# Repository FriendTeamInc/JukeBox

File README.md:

<p align="center">An affordable, adorable, powerful hotkey device to run macros, play funny sounds, managing your audio settings, change paint brush settings, configure items in OBS, and so much more!</p>

# Disclaimer
While this project is public, it is not ready for any sort of prime time. Any releases prior to 1.0 are considered beta.

## Docs
TODO

## Desktop Software
Made with Rust and egui for Windows and Linux, curates the user experience with the JukeBox.

### Building
It's as simple as running `cargo build --release`.

### Discord support
Discord, currently, will not provide support to new projects using their RPC protocol. Because of this, JukeBox Desktop will not support Discord out of the box, despite having functionality for it built in. To use the Discord functionality in JukeBox Desktop, you must do the following:
1. Go to https://discord.com/developers/applications/ and log in with your account.
2. Create a new application and name it JukeBoxDesktop.
3. Go to the OAuth2 settings tab.
4. Copy the client ID and client secret down to a safe location.
5. Set the redirect to `https://localhost:61961`. Save your changes.
6. Go to the App Testers settings tab.
7. Add your Discord account as a tester. An email will be sent to your account email, go to your inbox and accept the invite.
8. Build with the following command: `DISCORD_CLIENT_ID="<PUT_CLIENT_ID_HERE>" DISCORD_CLIENT_SECRET="<PUT_CLIENT_SECRET_HERE>" cargo run --features "discord" --release`.

## Device Firmware
TODO

### Building
1. (Linux only) Add yourself to the dialout group with the following: `sudo usermod -a -G dialout $USER`. Install the [RPi Pico udev rules](https://github.com/raspberrypi/picotool/blob/master/udev/99-picotool.rules). Add the following rules:
```
SUBSYSTEM=="usb", \
    ATTRS{idVendor}=="2e8a", \
    ATTRS{idProduct}=="000c", \
    TAG+="uaccess" \
    MODE="660", \  
    GROUP="plugdev"
```

2. Install the appropriate target toolchain: `rustup target add thumbv6m-none-eabi`.
3. Install [cmake](https://cmake.org/download/) for tool compilation.
4. (Linux only) Install libudev-dev: `sudo apt install libudev-dev`.
5. Install tools: `cargo install flip-link`.
5. Install tools: `cargo install --locked probe-rs-tools`. This is for installing firmware over Pico probe.
6. Run `cargo run -F "keypad"` to install the keypad firmware to the connected device. You can use pedalpad or knobpad too.

## Case
Made with OpenSCAD 2025.03.31 (development snapshot), protects everything inside the JukeBox. You can get the printable STLs with the `build.sh` script.

## PCB
Made with KiCad 10, the external brains of the JukeBox.

Footprints and models:
- [Cherry/Kailh Switch footprint based on this.](https://github.com/luke-schutt/Pi5Keyboard/blob/main/Pi5-pcb/Pi5Footprints.pretty/Low%20Profile%20GC%20plus%20MX.kicad_mod)

Estimated power usage is 5 volts at 0.1 amps, or 0.5 watts.

### Bill of Materials
| Ref            | Part No.               | Qty | Value | DNP |
|----------------|------------------------|-----|-------|-----|
| R1, R5, R14    | RMCF0402FT1K00         | 3   | 1k    |     |
| R3, R4         | RMCF0402FT27R0         | 2   | 27    |     |
| R6, R7         | RMCF0402FT5K11         | 2   | 5.11k |     |
| R8-11          | RMCF0402FT10K0         | 4   | 10k   |     |
| R12            | RMCF0402FT10K0         | 1   | 10k   |     |
| R13            | RMCF0402FT10R0         | 1   | 10    |     |
| R15            | RMCF0402FT33R0         | 1   | 33    |     |
| C1, C2         | GRM21BR61C106KE15K     | 2   | 10u   |     |
| C3, C4         | GCM1555C1H150JA16D     | 2   | 15p   |     |
| C5, C9, C11-18 | GRM155R71E104KE14J     | 10  | 100n  |     |
| C6-8, C10      | GRM155R60J475ME47D     | 4   | 4.7u  |     |
| L1             | AOTA-B201610S3R3-101-T | 1   | 3.3u  |     |
| D1-12          | 1N4148W-SOD-123        | 12  |       |     |
| D13-24         | WS2812B-2020           | 12  |       |     |
| D25            | 150080GS75000          | 1   |       |     |
| J1             | USB4105-GF-A           | 1   |       |     |
| Q1             | S8050-SOT-23           | 1   |       |     |
| SW1-12         | Keyboard Key Switch    | 12  |       |  X  |
| SW13           | PTS636SKG25SMTR LFS    | 1   |       |     |
| U1             | AZ1117IH-3.3TRG1       | 1   |       |     |
| U2             | W25Q32JVSSIQ           | 1   |       |     |
| U3             | RP2350A                | 1   |       |     |
| U4             | TFTQ-T20ST22ZP01       | 1   |       |  X  |
| U4             | FH34SRJ-22S-0.5SH(50)  | 1   |       |     |
| U5             | CAT24C128WI-GT3        | 1   |       |     |
| Y1             | ABM8-272-T3            | 1   |       |     |

# License
Copyright (c) 2020-2026 Logan "NotQuiteApex" Hickok-Dickson

All programming files, found in [`firmware/`](firmware/), [`software/`](software/), and [`case/`](case/), are licensed under the [MIT license](https://mit-license.org/).

All CAD files, found in [`hardware-pcb/`](hardware-pcb/), unless otherwise provided by an external source such as footprints or 3D models, are licesned under the [CC BY-NC-SA license](https://creativecommons.org/licenses/by-nc-sa/4.0/).

Both licenses can be found with the given links or as files in the root of this repostiory.

If you would like to sell a variation of the board designed by you, reach out and an alternative license can be discussed and granted.

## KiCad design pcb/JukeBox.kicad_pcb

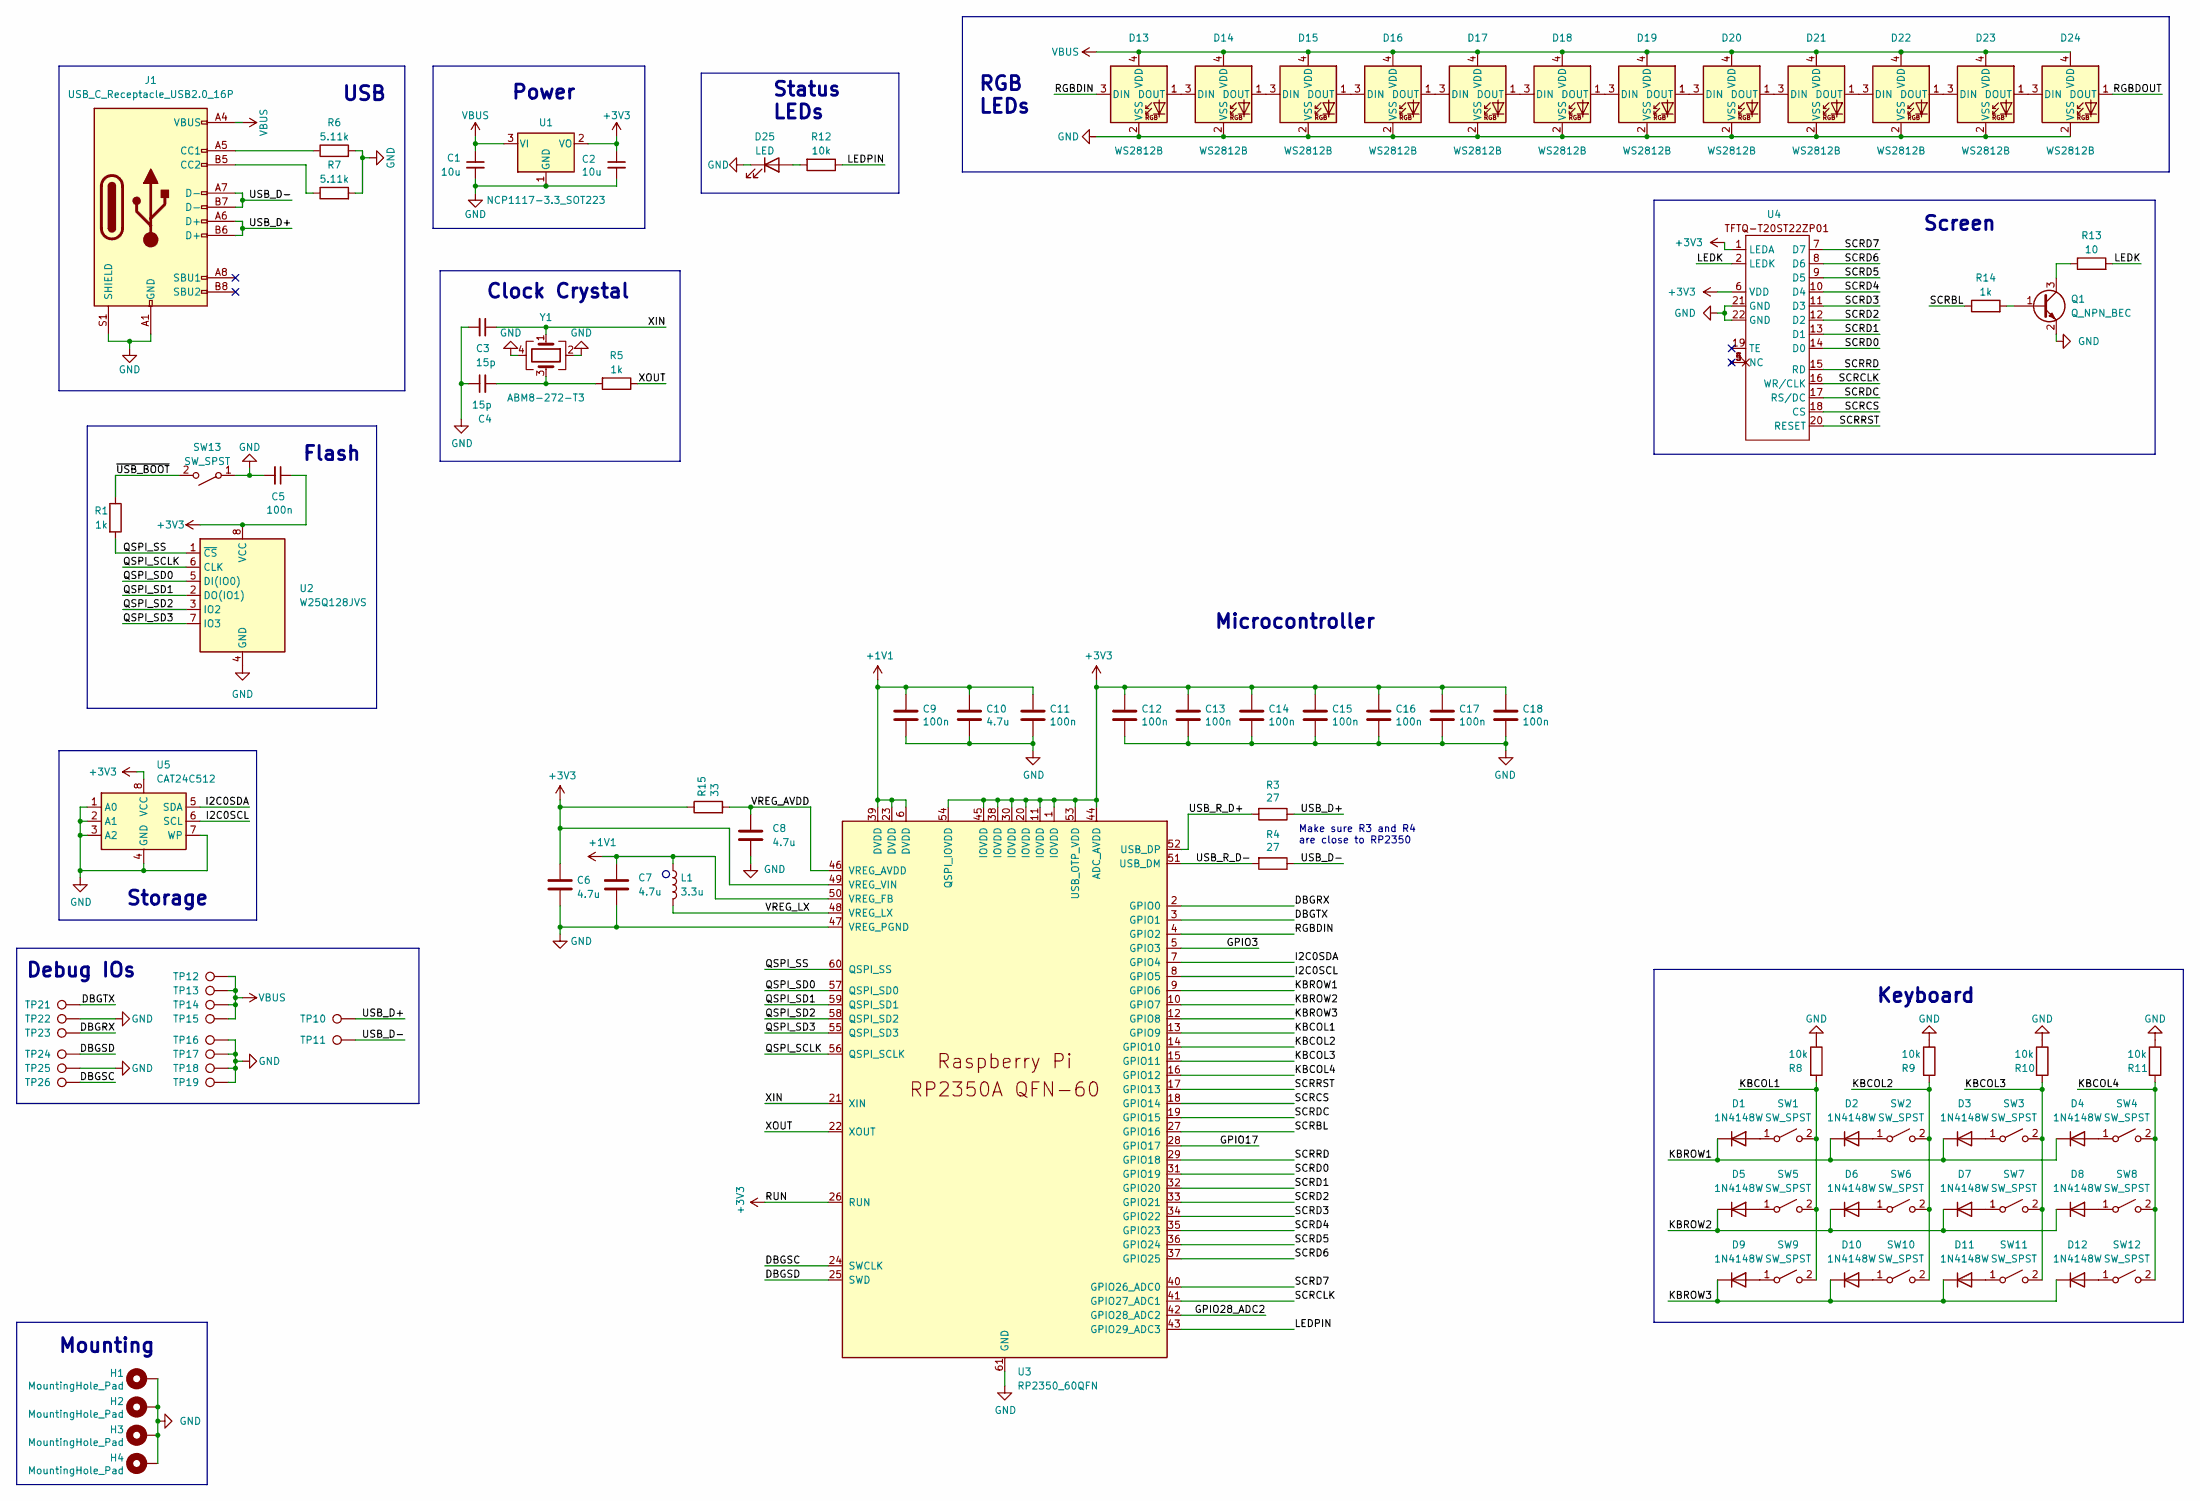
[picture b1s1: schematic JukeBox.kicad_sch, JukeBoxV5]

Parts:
C1, C2: 10u; C_0805_2012Metric
C3, C4: 15p; C_0402_1005Metric
C5, C9, C11, C12, C13, C14, C15, C16, C17, C18: 100n; C_0402_1005Metric
C6, C7, C8, C10: 4.7u; C_0402_1005Metric
D1, D2, D3, D4, D5, D6, D7, D8, D9, D10, D11, D12: 1N4148W; D_SOD-123
D13, D14, D15, D16, D17, D18, D19, D20, D21, D22, D23, D24: WS2812B; LED_WS2812B-2020_PLCC4_2.0x2.0mm
D25: LED; D_0805_2012Metric_Pad1.15x1.40mm_HandSolder
H1, H2, H3, H4: MountingHole_Pad; MountingHole_3.2mm_M3_Pad_Via
J1: USB_C_Receptacle_USB2.0_16P; USB_C_Receptacle_GCT_USB4105-xx-A_16P_TopMnt_Horizontal
L1: 3.3u; L_pol_2016
Q1: Q_NPN_BEC; SOT-23
R1, R5, R14: 1k; R_0402_1005Metric
R3, R4: 27; R_0402_1005Metric
R6, R7: 5.11k; R_0402_1005Metric
R8, R9, R10, R11, R12: 10k; R_0402_1005Metric
R13: 10; R_0402_1005Metric
R15: 33; R_0402_1005Metric
SW1, SW2, SW3, SW4, SW5, SW6, SW7, SW8, SW9, SW10, SW11, SW12: SW_SPST; ALLKEY
SW13: SW_SPST; SW_SPST_CK_RS282G05A3
TP10, TP11, TP12, TP13, TP14, TP15, TP16, TP17, TP18, TP19, TP21, TP22, TP23, TP24, TP25, TP26: TestPoint; TestPoint_Pad_D1.5mm
U1: NCP1117-3.3_SOT223; SOT-223-3_TabPin2
U2: W25Q128JVS; SOIC-8_5.23x5.23mm_P1.27mm
U3: RP2350_60QFN; RP2350-QFN-60-1EP_7x7_P0.4mm_EP3.4x3.4mm_ThermalVias
U4: TFTQ-T20ST22ZP01
U5: CAT24C512; SOIC-8_3.9x4.9mm_P1.27mm
Y1: ABM8-272-T3; Crystal_SMD_Abracon_ABM8G-4Pin_3.2x2.5mm

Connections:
+1V1: C7.1, C9.1, C10.1, C11.1, L1.1, U3.6 (DVDD), U3.23 (DVDD), U3.39 (DVDD), U3.50 (VREG_FB)
+3V3: C2.1, C5.1, C6.1, C12.1, C13.1, C14.1, C15.1, C16.1, C17.1, C18.1, R15.1, U1.2 (VO), U2.8 (VCC), U3.1 (IOVDD), U3.11 (IOVDD), U3.20 (IOVDD), U3.26 (RUN), U3.30 (IOVDD), U3.38 (IOVDD), U3.44 (ADC_AVDD), U3.45 (IOVDD), U3.49 (VREG_VIN), U3.53 (USB_OTP_VDD), U3.54 (QSPI_IOVDD), U4.1 (LEDA), U4.6 (VDD), U5.8 (VCC)
/DBGRX: TP23.1, U3.2 (GPIO0)
/DBGSC: TP26.1, U3.24 (SWCLK)
/DBGSD: TP24.1, U3.25 (SWD)
/DBGTX: TP21.1, U3.3 (GPIO1)
/GPIO3: U3.5 (GPIO3)
/GPIO17: U3.28 (GPIO17)
/GPIO28_ADC2: U3.42 (GPIO28_ADC2)
/I2C0SCL: U3.8 (GPIO5), U5.6 (SCL)
/I2C0SDA: U3.7 (GPIO4), U5.5 (SDA)
/KBCOL1: R8.2, SW1.2 (B), SW5.2 (B), SW9.2 (B), U3.13 (GPIO9)
/KBCOL2: R9.2, SW2.2 (B), SW6.2 (B), SW10.2 (B), U3.14 (GPIO10)
/KBCOL3: R10.2, SW3.2 (B), SW7.2 (B), SW11.2 (B), U3.15 (GPIO11)
/KBCOL4: R11.2, SW4.2 (B), SW8.2 (B), SW12.2 (B), U3.16 (GPIO12)
/KBROW1: D1.2 (K), D2.2 (K), D3.2 (K), D4.2 (K), U3.9 (GPIO6)
/KBROW2: D5.2 (K), D6.2 (K), D7.2 (K), D8.2 (K), U3.10 (GPIO7)
/KBROW3: D9.2 (K), D10.2 (K), D11.2 (K), D12.2 (K), U3.12 (GPIO8)
/LEDK: R13.2, U4.2 (LEDK)
/LEDPIN: R12.1, U3.43 (GPIO29_ADC3)
/QSPI_SCLK: U2.6 (CLK), U3.56 (QSPI_SCLK)
/QSPI_SD0: U2.5 (DI(IO0)), U3.57 (QSPI_SD0)
/QSPI_SD1: U2.2 (DO(IO1)), U3.59 (QSPI_SD1)
/QSPI_SD2: U2.3 (IO2), U3.58 (QSPI_SD2)
/QSPI_SD3: U2.7 (IO3), U3.55 (QSPI_SD3)
/QSPI_SS: R1.2, U2.1 (~CS), U3.60 (QSPI_SS)
/RGBDIN: D13.3 (DIN), U3.4 (GPIO2)
/RGBDOUT: D24.1 (DOUT)
/SCRBL: R14.1, U3.27 (GPIO16)
/SCRCLK: U3.41 (GPIO27_ADC1), U4.16 (WR/CLK)
/SCRCS: U3.18 (GPIO14), U4.18 (CS)
/SCRD0: U3.31 (GPIO19), U4.14 (D0)
/SCRD1: U3.32 (GPIO20), U4.13 (D1)
/SCRD2: U3.33 (GPIO21), U4.12 (D2)
/SCRD3: U3.34 (GPIO22), U4.11 (D3)
/SCRD4: U3.35 (GPIO23), U4.10 (D4)
/SCRD5: U3.36 (GPIO24), U4.9 (D5)
/SCRD6: U3.37 (GPIO25), U4.8 (D6)
/SCRD7: U3.40 (GPIO26_ADC0), U4.7 (D7)
/SCRDC: U3.19 (GPIO15), U4.17 (RS/DC)
/SCRRD: U3.29 (GPIO18), U4.15 (RD)
/SCRRST: U3.17 (GPIO13), U4.20 (RESET)
/USB_D+: J1.A6 (D+), J1.B6 (D+), R3.1, TP10.1
/USB_D-: J1.A7 (D-), J1.B7 (D-), R4.1, TP11.1
/USB_R_D+: R3.2, U3.52 (USB_DP)
/USB_R_D-: R4.2, U3.51 (USB_DM)
/VREG_AVDD: C8.1, R15.2, U3.46 (VREG_AVDD)
/VREG_LX: L1.2, U3.48 (VREG_LX)
/XIN: C3.1, U3.21 (XIN), Y1.1
/XOUT: R5.1, U3.22 (XOUT)
/~USB_BOOT: R1.1, SW13.2 (B)
GND: C1.2, C2.2, C3.2, C4.1, C5.2, C6.2, C7.2, C8.2, C9.2, C10.2, C11.2, C12.2, C13.2, C14.2, C15.2, C16.2, C17.2, C18.2, D13.2 (VSS), D14.2 (VSS), D15.2 (VSS), D16.2 (VSS), D17.2 (VSS), D18.2 (VSS), D19.2 (VSS), D20.2 (VSS), D21.2 (VSS), D22.2 (VSS), D23.2 (VSS), D24.2 (VSS), D25.1 (K), H1.1, H2.1, H3.1, H4.1, J1.A1 (GND), J1.A12 (GND), J1.B1 (GND), J1.B12 (GND), J1.S1 (SHIELD), Q1.2 (E), R6.2, R7.2, R8.1, R9.1, R10.1, R11.1, SW13.1 (A), TP16.1, TP17.1, TP18.1, TP19.1, TP22.1, TP25.1, U1.1 (GND), U2.4 (GND), U3.47 (VREG_PGND), U3.61 (GND), U4.21 (GND), U4.22 (GND), U5.1 (A0), U5.2 (A1), U5.3 (A2), U5.4 (GND), U5.7 (WP), Y1.2, Y1.4
unnamed: C4.2, R5.2, Y1.3
unnamed: D1.1 (A), SW1.1 (A)
unnamed: D2.1 (A), SW2.1 (A)
unnamed: D3.1 (A), SW3.1 (A)
unnamed: D4.1 (A), SW4.1 (A)
unnamed: D5.1 (A), SW5.1 (A)
unnamed: D6.1 (A), SW6.1 (A)
unnamed: D7.1 (A), SW7.1 (A)
unnamed: D8.1 (A), SW8.1 (A)
unnamed: D9.1 (A), SW9.1 (A)
unnamed: D10.1 (A), SW10.1 (A)
unnamed: D11.1 (A), SW11.1 (A)
unnamed: D12.1 (A), SW12.1 (A)
unnamed: D13.1 (DOUT), D14.3 (DIN)
unnamed: D14.1 (DOUT), D15.3 (DIN)
unnamed: D15.1 (DOUT), D16.3 (DIN)
unnamed: D16.1 (DOUT), D17.3 (DIN)
unnamed: D17.1 (DOUT), D18.3 (DIN)
unnamed: D18.1 (DOUT), D19.3 (DIN)
unnamed: D19.1 (DOUT), D20.3 (DIN)
unnamed: D20.1 (DOUT), D21.3 (DIN)
unnamed: D21.1 (DOUT), D22.3 (DIN)
unnamed: D22.1 (DOUT), D23.3 (DIN)
unnamed: D23.1 (DOUT), D24.3 (DIN)
unnamed: D25.2 (A), R12.2
unnamed: J1.A5 (CC1), R6.1
unnamed: J1.B5 (CC2), R7.1
unnamed: Q1.1 (B), R14.2
unnamed: Q1.3 (C), R13.1
VBUS: C1.1, D13.4 (VDD), D14.4 (VDD), D15.4 (VDD), D16.4 (VDD), D17.4 (VDD), D18.4 (VDD), D19.4 (VDD), D20.4 (VDD), D21.4 (VDD), D22.4 (VDD), D23.4 (VDD), D24.4 (VDD), J1.A4 (VBUS), J1.A9 (VBUS), J1.B4 (VBUS), J1.B9 (VBUS), TP12.1, TP13.1, TP14.1, TP15.1, U1.3 (VI)

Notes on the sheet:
Flash
Mounting
Make sure R3 and R4 are close to RP2350
Debug IOs
Storage
Keyboard
USB
RGB LEDs
Screen
Power
Clock Crystal
Microcontroller
Status LEDs

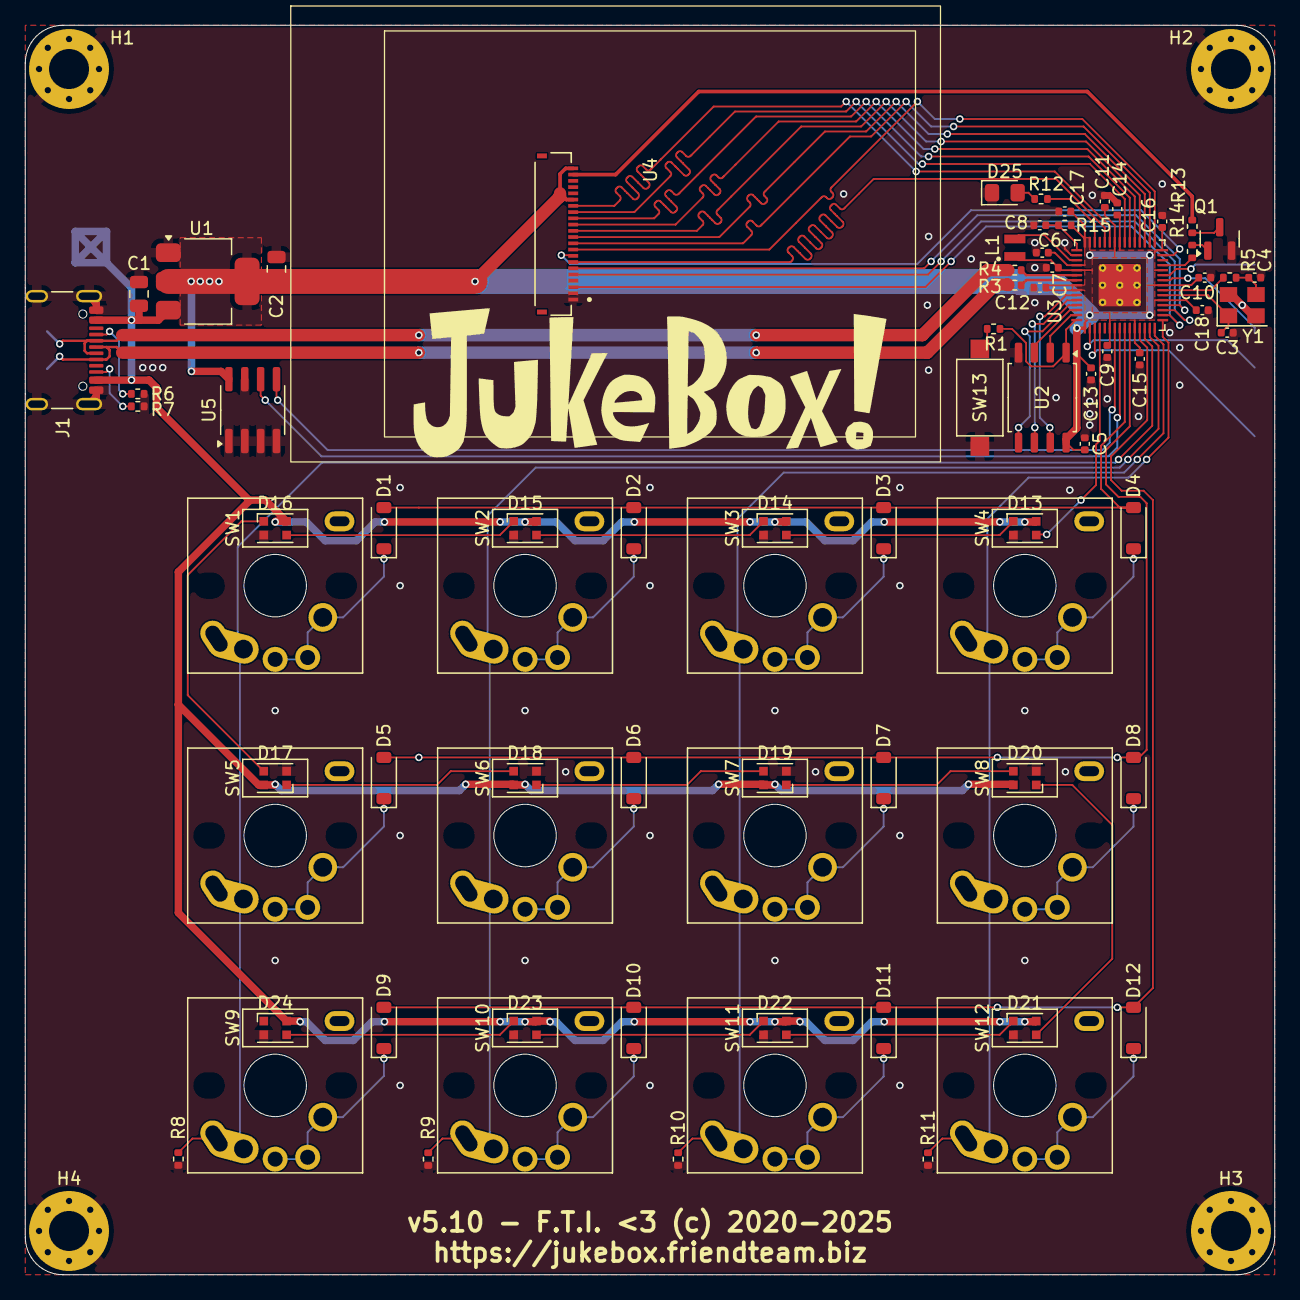
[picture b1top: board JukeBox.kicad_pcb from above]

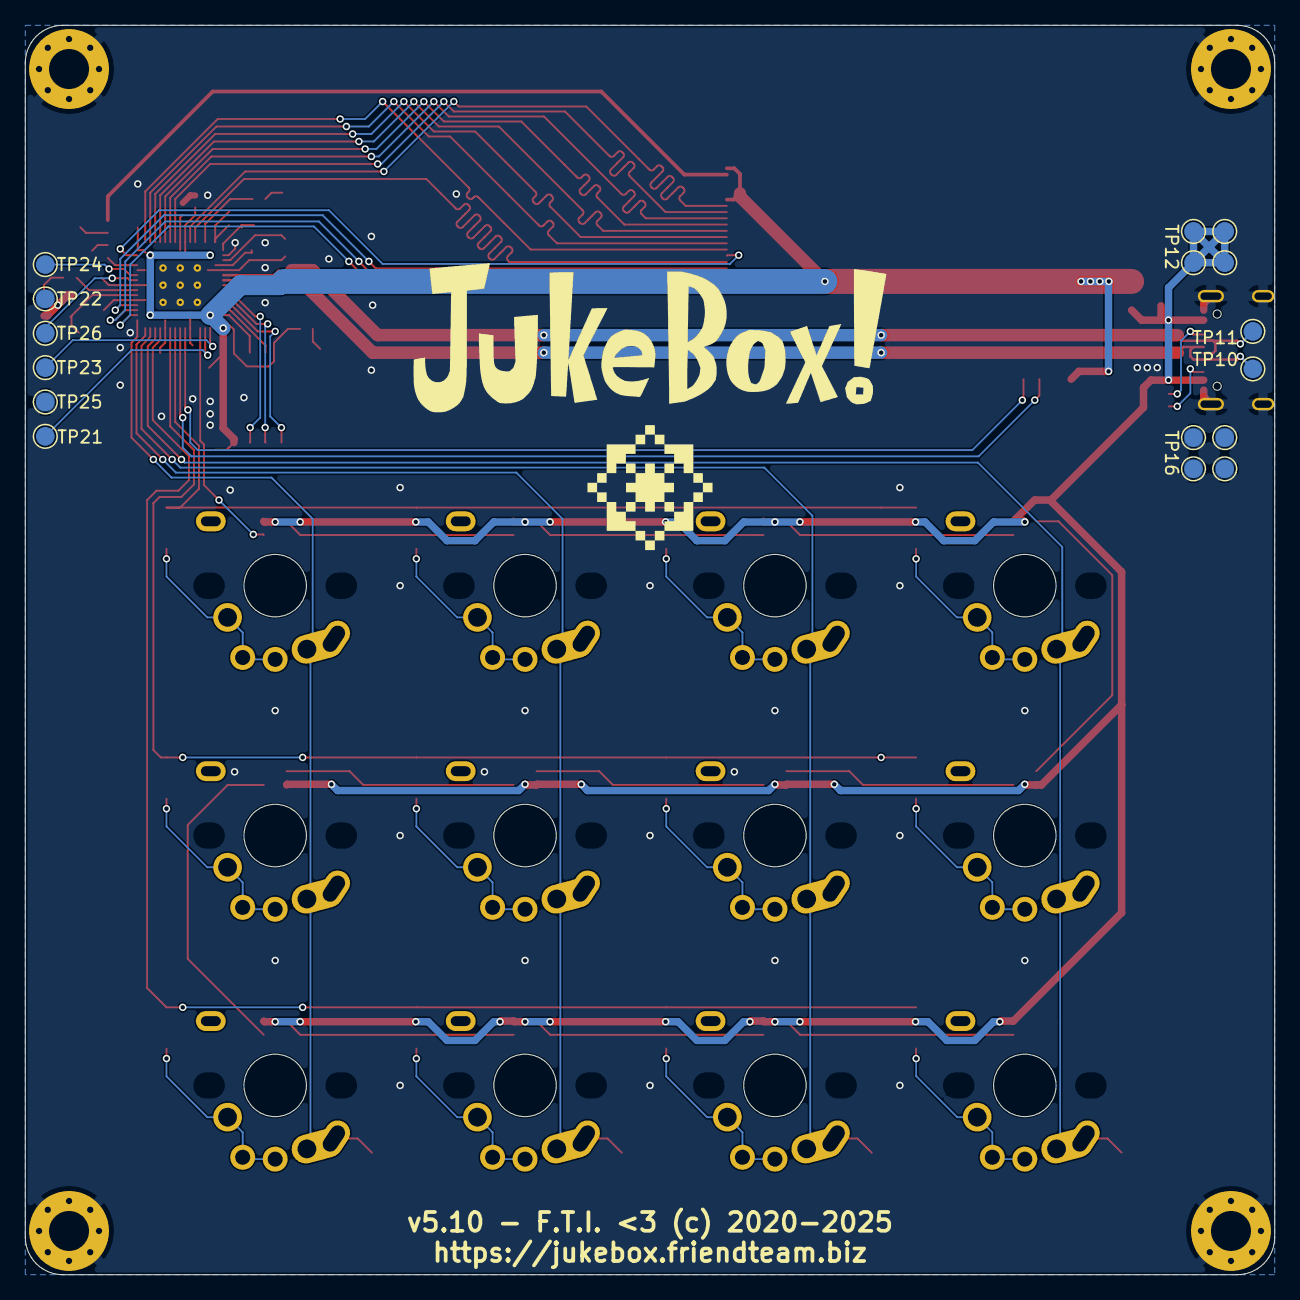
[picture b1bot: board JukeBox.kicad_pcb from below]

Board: 2 copper layers, 100.0 x 100.0 mm, 101 parts (17 on the bottom side), 78 nets.

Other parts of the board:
G1, G1#2: LOGO; JukeBox

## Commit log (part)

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2025-02-16 update desktop app dependencies and some minor ui updates
2025-02-16 switch to direct rp2040-hal, update appropriately.
    TODO: update rp2040-flash when ready
2025-02-16 fix annoying warnings
2025-02-17 fix bootloader
2025-03-01 update gui to start on reaction editing
2025-03-02 add basic device management, each profile accounts for every device
2025-03-02 remove current device from config, move it to gui state, reduce need for config accesses
2025-03-02 add saving and loading of config
2025-03-02 add pedal module for firmware, begin support for it on desktop
2025-03-03 fix up multi-threading for multi-device usage
2025-03-04 fix pedalpad firmware, update firmware cargo, update software cargo, rework reactions
2025-03-04 fix reactions looking up things incorrectly, various other minor updates
2025-03-04 add url opening, add ui editing for reactions (incomplete)
2025-03-04 add application executing
2025-03-05 add meta copy from profile and switch profile
2025-03-05 back button is save, prevent multi-level copy from action
2025-03-05 fix connection inability when trying to connect multiple devices
2025-03-05 outlining more reactions
2025-03-07 start on discord reactions
2025-03-07 update device name, add update page to gui
2025-03-07 add result type for reactions
2025-03-09 start on async
2025-03-09 move more things to runtime, but cant close application
2025-03-09 fix tokio::spawn
2025-03-10 switch mutex to tokio kind
2025-03-10 more awaiting in serial
2025-03-10 auto-switch to first connected device, make system launch app async, fix test key
2025-03-10 have bad configs be saved as old, show devices and profiles alphabetically, prevent devices having the same name by renaming
2025-03-11 update chores
2025-03-11 move a bunch of mapping stuff out of types.rs
2025-03-11 cleanup
2025-03-11 even more formatting
2025-03-11 start on i18n work
2025-03-11 major restructure
    thank god im doing this before any kind of release huh
2025-03-11 forgot to save
2025-03-11 localizify system and soundboard
2025-03-11 localizify obs.rs
2025-03-12 basic discord integration working
2025-03-12 add discord as a feature, add push to deafen
2025-03-12 add push-to-(do-thing)'s
2025-03-12 updated note on test key
2025-03-12 add token refreshing for discord, update action to get actual config, batch futures for key inputs
2025-03-12 make discord and reqwest optional dependencies
2025-03-13 preliminary work on adding identify command
2025-03-13 add identify to gui
2025-03-13 convert to run_native
2025-03-15 begin rgb control for keypad
2025-03-15 change RGBControl to RgbProfile, add some notes
2025-03-16 begin on rgb editing
2025-03-16 finish rainbows
2025-03-16 finish setting rgb
2025-03-16 have RGB updated on profile switch
2025-03-16 add rgb preview
2025-03-16 fix rgb not starting on connection, add connection status to firmware for other modules to reference
2025-03-16 minor adjustments for default keypad behavior
2025-03-17 round corners of rgb boxes
2025-03-18 more work on obs actions, get obs client set up
2025-03-18 add toggle source for obs
2025-03-18 add scene (and preview) switching
2025-03-18 update translation strings
2025-03-19 switch from enum to string
2025-03-19 add scene collection switch
2025-03-19 more to_string -> into
2025-03-20 update icon work, update default rgb work, update crates
2025-03-20 update icons for input, update config defaults
2025-03-21 switch to 16 bit screen driver
2025-03-22 more clean example of icons on screen
2025-03-22 add timing results for screen graphics
2025-03-24 clear framebuffer via dma
2025-03-24 unfinished dma for pio
2025-03-24 use dma for clearing framebuffer
2025-03-24 icon slots in ram, process effect for pressing keys
2025-03-25 reset icons as necessary
2025-03-25 update all icons to be 32x32
2025-03-25 change icon filtering back to nearest
2025-03-25 obs icons
2025-03-26 update protocol
2025-03-27 add icon animations for firmware
2025-03-27 add save and exit modal for editing the device
2025-03-27 fix software building for my fork of discord rpc
2025-03-28 update firmware builds
2025-03-28 remove nightly links, not working anymore
2025-03-29 load images over serial
2025-03-31 Initial commit.
2025-04-01 switch to async reqwest api
2025-04-01 make discord more async, move reqwest to async
2025-04-02 preview keys selected in input keyboard action
2025-04-02 fix broken hardware buttons with old actions
2025-04-03 add modal for error messages
2025-04-03 use device nickname instead of uid
2025-04-04 add hiding to system tray
2025-04-04 fix linux build for desktop
2025-04-04 fix gtk dep for windows (aka remove it)
2025-04-04 add custom icons for actions
2025-04-05 start on system audio control (for linux only rn)
2025-04-05 add source and sink adjustment
2025-04-05 fix windows cross build
2025-04-05 change windows stuff to todo!()'s
2025-04-05 better handle creating source and sink controllers for linux
2025-04-05 build out event loop for audio instead of the previous system
2025-04-05 add methods for adjusting volume on windows
2025-04-05 fix return type for get_devices()
2025-04-06 overhaul options for soundboard
2025-04-06 update crates for firmware, add back embedded graphics for screen drawing
2025-04-07 properly transpose the screen such that the top left corner of the device is the origin
2025-04-07 disable pedalpad firmware building for now (in ci)
2025-04-07 prepare for profile name transfer
2025-04-07 some fixes, add more function for gui to update device screen
2025-04-08 fix screen setting, add screen setting to firmware
2025-04-08 minor fixes for saving
2025-04-08 add sysinfo and start thread for it
2025-04-09 push system stats over the wire
2025-04-09 add gpu monitoring
2025-04-09 fix crate versions
2025-04-10 update rocm, lock gpu stuff behind feature (for now?)
2025-04-12 add software update thread for checking for updates on github
2025-04-13 add modal popup for updates
2025-04-13 minor updates to the firmware update page
2025-04-19 update screen cutout and add cutout for flash button on top case
2025-04-21 final adjustments for case for beta test
2025-06-02 update desktop deps, add version info to update notifier.
2025-06-02 bump firmware version
2025-06-04 fix some crashes and disable some unfinished stuff, and expand the window vertically
2025-06-04 finish screen brightness configuration, and bump version
2025-06-04 fix missing dep for firmware action script
2025-06-04 fix paths in action scripts
2025-06-04 fix windows artifact in action build
2025-06-04 change firmware to be release instead of debug in action build
2025-06-08 bump version
2025-06-08 switch from dyn trait to enum for sanity
2025-06-08 update changelog, only show popup for saving when changes were made
2025-06-10 add error popup for updating firmware, allow console on windows, and fix firmware eventually freezing
2025-06-12 fix icon device upload in async context
2025-06-12 update dependencies for desktop for picoboot fix, add message to firmware update error screen
2025-06-13 disable usb storage for firmware mode, fix firmware update error screen ok button, revert tray functionality for windows, force serial timeout to be 100 milliseconds
2025-06-13 further adjust usb serial internal buffer sizes
2025-06-13 fix changelog
2025-06-13 automatically resize icons, add popup for failing to load the config, connection status is more prominent
2025-06-13 fix inability to leave other screens when an update fails, reformat some cargo.tomls
2025-06-15 add mouse event, bunch of usb fixes, update some dependencies
2025-06-15 fix iad configuration for windows and enable control buffer 256 for usb-device crate
2025-06-16 improve switch profile targetting deleted/modified profiles and disable cpu temp on windows
2025-06-21 add log for device uid and firmware version on connect, fix application remembering device firmware when disconnected
2025-06-21 clear serial buffer when resetting connection, fix default naming on device connection
    these are temporary fixes for a problem that needs further investigation
2025-06-22 fix nickname collisions on new device added, fix device not receiving the initial configuration on first connection
2025-06-22 fix keyboard key requests being way too fast, only send RGB and Screen packets to keypad devices as futureproofing
2025-06-26 massive pcb rework for rp2350
2025-06-27 add new screen footprint and route traces. update bom
2025-06-27 add welcome message on startup
2025-06-27 fix some todo's, switch serialconnectiondetails to just use device type
2025-06-27 added wave pattern for rgb (finally!)
2025-06-27 update locale file, add a bunch of defaults to util (from gui)
2025-06-28 disable some old workflows
2025-06-28 add nvidia gpu monitoring support by default, update dependencies, bump version
2025-06-28 update documentation to point to other docs
2025-06-28 more doc updates
2025-06-28 update changelog, remove old workflows
2025-06-29 update case to fit new screen and pcb better
2025-06-29 finalize screen placement on pcb, add spacer to scad, add bumps to legs for binding to the case better
2025-06-30 big print plate of parts for case, fix leg brace calculation
2025-07-06 update to new part on pcb for screen
2025-07-06 update bom
2025-07-12 start on eeprom support, allow more colors for breathe and wave rgb patterns
2025-07-13 some eeprom notes for later
2025-07-13 add bootsel button instead of pad
2025-07-14 finalize pinout and routing for screen, add models for missing components
2025-07-16 update part numbers
2025-07-25 switch to bincode for encoding/decoding data, lots of work on eeprom
2025-07-25 let mutex functions return stuff, lots of formatting changes, update identify function to not seem as buggy
2025-07-25 add update function for eeprom
2025-07-26 unify input event setting in protocol
2025-07-27 adjust some default behaviors, add a key select for static per key rgb
2025-08-02 allow profile name to be hidden, update changelog, update a lot of constants
2025-08-03 add suspend detection, doesnt work?
2025-08-04 increase serial buffer size, update some imports
2025-08-05 start switch to embassy
2025-08-05 fix cicd, add uid, start on usb
2025-08-05 build out usb comms, indicate suspended status on led, fix cicd builds properly
2025-08-06 update dependencies
2025-08-06 fix firmware crash, fix icon size in software, fix version numberings
2025-08-09 update case for debug port cutout
2025-08-09 add keypad task
2025-08-10 pipe serial data from usb task to serial task
2025-08-10 stub the serial commands, add reading of keyboard for serial connection
2025-08-10 minor change to inputs, usb task
2025-08-10 add rgb profiles, adjust util for calculating things
2025-08-11 start outlining screen module
2025-08-11 finish screen driver, add some test code for it
2025-08-12 start on screen function porting
2025-08-12 more screen work. draw function is locking things up, fix that later
2025-08-14 update pcb to add missing pin for screen
    ugh
2025-08-14 DNP updates for BOM
2025-09-04 fix screen driver not working, add scr_rd pin for newer boards to control
2025-09-04 code style fix
2025-10-11 fix missing pre-tick draw on startup
2025-11-21 add default icons back to screen
2025-12-31 code style cleanup, fix rgb access in gui
2026-01-06 updated screen configuration for device
2026-01-08 update dependencies, allow input events
2026-01-09 fix colors of rgb preview in software
2026-01-24 fix temperature reporting for my CPU
2026-04-24 fix firmware not building (rearrange firmware irq binds)
2026-04-25 fix dimming
2026-04-25 harder overclock, adjust dimming curve
2026-04-25 remove pixel transposing and configure display to read memory in correct orientation
2026-04-26 minor adjustments to the case top
2026-04-29 improve obs connectivity
2026-04-30 remove some old obs stuff, dynamic icon for discord mute and deafen
2026-05-02 add custom icons for actions with dynamic icons
2026-05-03 re-enable systray support for windows
2026-05-04 remove pactl-rs (gpl reasons) and just use libpulse-binding
2026-05-04 update chagelog, add feature switch for log mode, minor adjustment to discord authentication at launch
2026-05-30 allow errors with OBS actions to disconnect from the websocket
2026-05-30 minor updates to logging
2026-05-30 add duplicate profile button, switch profiles whenever the new or dupe button is pressed, and update dependencies
2026-05-30 update workflows
2026-05-31 fix dnp for key resistors
2026-06-04 shorten pcb to reduce cost
2026-06-29 add more descript errors for discord error reporting
2026-06-29 better format errors from discord
2026-06-30 log all action errors on creation, fix double authenticate with discord

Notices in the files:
pcb/JukeBox.kicad_pcb:
v5.10 - F.T.I. <3 (c) 2020-2025
